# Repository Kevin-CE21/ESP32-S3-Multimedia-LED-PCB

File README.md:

# ESP32-S3 Multimedia & LED Control PCB (KiCad)

A 2-layer, heart-shaped carrier PCB that combines an ESP32-S3, 28 PWM-dimmed LEDs, a TFT display with microSD, and I2S audio on one USB-C-powered board. Designed from scratch in KiCad, from schematic through layout.

## PCB Layout

## Schematic

## 3D Model

## Board (Front)

## Board (Back)

## Overview

The board is a carrier for an ESP32-S3-DevKitC-1 module. It takes 5 V from a USB-C connector, drives 28 LEDs through two daisy-chained TLC5940 16-channel PWM drivers, shows graphics on an ILI9341 TFT, reads files from that display's microSD slot, and plays audio through a MAX98357A I2S class-D amplifier and speaker. Two pushbuttons provide user input.

## Hardware

| Ref | Part | Role |
| --- | --- | --- |
| U6 | ESP32-S3-DevKitC-1-N16R8V | Microcontroller, Wi-Fi, 3.3 V logic supply |
| U2, U4 | TLC5940NT | 16-channel, 12-bit PWM constant-current LED drivers (daisy-chained) |
| D1–D28 | LEDs | 28 PWM-controlled LEDs |
| U1 | ILI9341 TFT module with microSD | Display and file storage over SPI |
| U5 | MAX98357A (Adafruit 3006) | I2S class-D audio amplifier |
| J3 | USB-C receptacle (power only) | 5 V input |
| R1, R2 | 5.1 kΩ | USB-C CC pull-downs (power sink) |
| R3, R4 | 3.9 kΩ | TLC5940 IREF current-set resistors |
| C4, C5, C9, C10 | 100 nF | Local decoupling |
| C2 | 10 µF | Bulk capacitance |
| SW1, SW2 | Pushbuttons | User input |

## System Design

**Power**
- USB-C power-only receptacle with 5.1 kΩ pull-downs on CC1 and CC2, so any USB-C charger supplies 5 V.
- 5 V feeds the LED drivers, LEDs and audio amplifier; the DevKitC's onboard regulator supplies 3.3 V to logic.
- 100 nF decoupling at each IC plus 10 µF bulk capacitance.

**LED control**
- Two TLC5940s chained on one serial bus: the ESP32 shifts data into the first driver (SIN), and its SOUT feeds the second. Shared SCLK, XLAT, BLANK and GSCLK lines control both.
- 28 of the 32 available channels drive LEDs (all 16 on one driver, 12 on the other).
- Per-channel current is set by the IREF resistor: I = (1.24 V / 3.9 kΩ) × 31.5 ≈ 10 mA, about 280 mA with every LED fully on.

**Display and storage**
- The TFT and microSD share one SPI bus (SCK, MOSI, MISO) with separate chip selects (CS, SD_CS) plus D/C and RESET lines for the display.

**Audio**
- Dedicated I2S lines (BCLK, LRCLK, DIN) from the ESP32 to the MAX98357A, which drives the speaker directly.

## Design Considerations

- Trace widths sized to current: wider traces for 5 V power and LED loads, 0.5 mm traces for logic signals.
- Power and high-current paths kept short; decoupling placed next to each driver.
- ERC and DRC checks run before fabrication.

## Repository Contents

- `hardware/SosoGift.kicad_sch`: schematic
- `hardware/SosoGift.kicad_pro`: KiCad project file
- `images/`: layout, schematic and 3D renders

## Skills Demonstrated

- Schematic capture and PCB layout in KiCad
- Power input design (USB-C sink) and power distribution
- Constant-current LED driver design and current budgeting
- SPI and I2S peripheral integration
- Component selection and design rule verification

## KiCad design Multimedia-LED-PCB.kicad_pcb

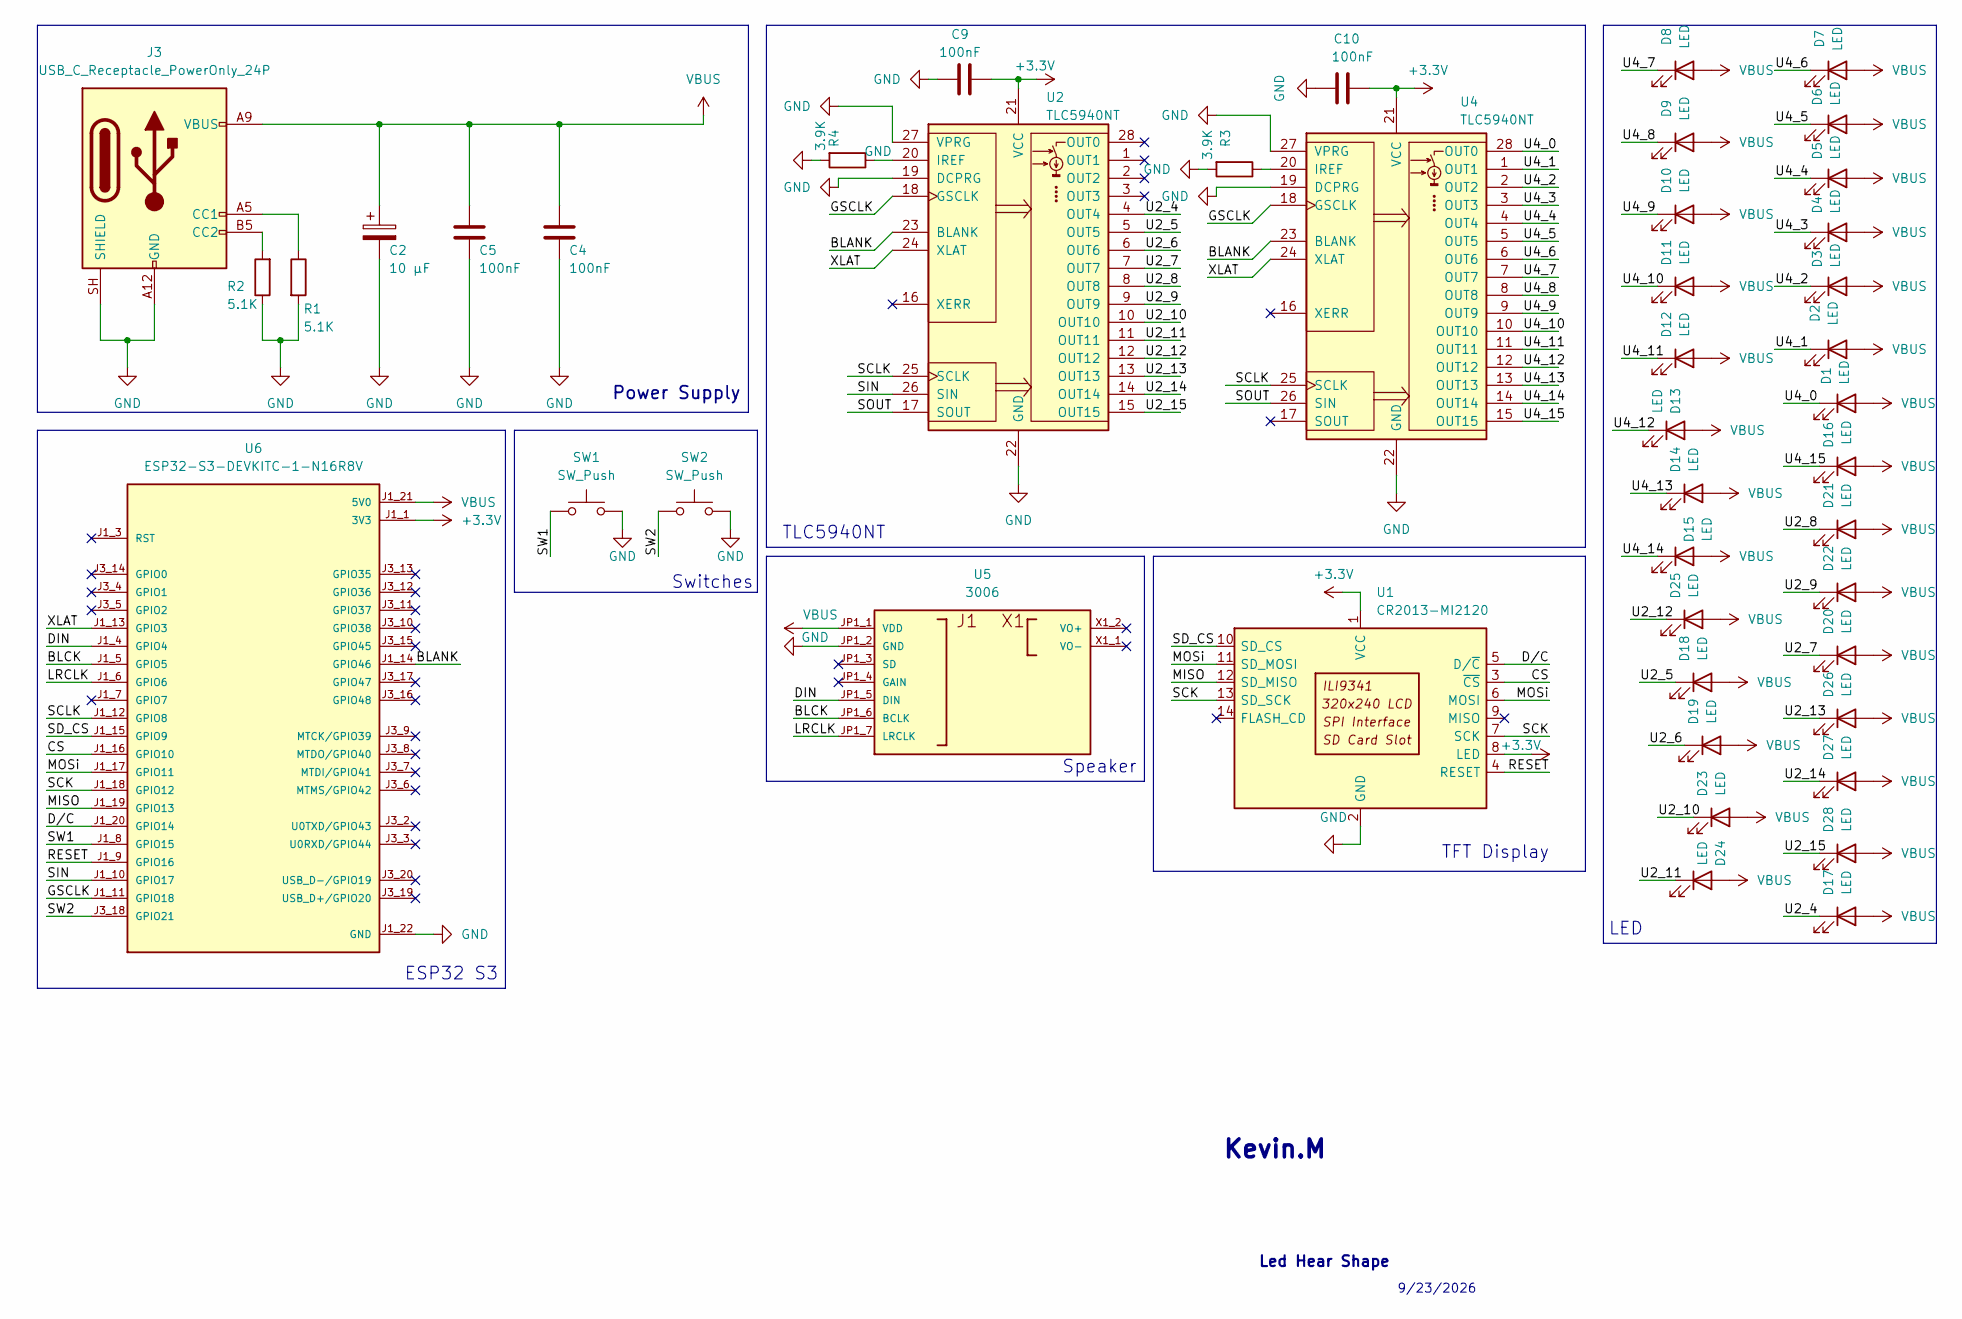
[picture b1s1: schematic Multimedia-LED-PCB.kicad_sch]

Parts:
C2: 10 µF; C_0805_2012Metric
C4, C5, C9, C10: 100nF; C_0603_1608Metric
D1, D2, D3, D4, D5, D6, D7, D8, D9, D10, D11, D12, D13, D14, D15, D16, D17, D18, D19, D20, D21, D22, D23, D24, D25, D26, D27, D28: LED; LED_D5.0mm
J3: USB_C_Receptacle_PowerOnly_24P; USB_C_Receptacle_GCT_USB4135-GF-A_6P_TopMnt_Horizontal; Part# C5438410
R1, R2: 5.1K; R_0603_1608Metric
R3, R4: 3.9K; R_0603_1608Metric
SW1, SW2: SW_Push; SW_PUSH-12mm
U1: CR2013-MI2120
U2, U4: TLC5940NT; DIP-28_W7.62mm
U5: 3006; MODULE_3006; PARTREV A
U6: ESP32-S3-DEVKITC-1-N16R8V; XCVR_ESP32-S3-DEVKITC-1-N16R8V; PARTREV 1.1

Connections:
+3.3V: C9.2, C10.2, U1.1 (VCC), U1.8 (LED), U2.21 (VCC), U4.21 (VCC), U6.J1_1 (3V3), U6.J1_2 (3V3)
/BLANK: U2.23 (BLANK), U4.23 (BLANK), U6.J1_14 (GPIO46)
/BLCK: U5.JP1_6 (BCLK), U6.J1_5 (GPIO5)
/CS: U1.3 (~CS), U6.J1_16 (GPIO10)
/DIN: U5.JP1_5 (DIN), U6.J1_4 (GPIO4)
/D/C: U1.5 (D/~C), U6.J1_20 (GPIO14)
/GSCLK: U2.18 (GSCLK), U4.18 (GSCLK), U6.J1_11 (GPIO18)
/LRCLK: U5.JP1_7 (LRCLK), U6.J1_6 (GPIO6)
/MISO: U1.12 (SD_MISO), U6.J1_19 (GPIO13)
/MOSi: U1.6 (MOSI), U1.11 (SD_MOSI), U6.J1_17 (GPIO11)
/RESET: U1.4 (RESET), U6.J1_9 (GPIO16)
/SCK: U1.7 (SCK), U1.13 (SD_SCK), U6.J1_18 (GPIO12)
/SCLK: U2.25 (SCLK), U4.25 (SCLK), U6.J1_12 (GPIO8)
/SD_CS: U1.10 (SD_CS), U6.J1_15 (GPIO9)
/SIN: U2.26 (SIN), U6.J1_10 (GPIO17)
/SOUT: U2.17 (SOUT), U4.26 (SIN)
/SW1: SW1.1, U6.J1_8 (GPIO15)
/SW2: SW2.1, U6.J3_18 (GPIO21)
/U2_4: D17.1 (K), U2.4 (OUT4)
/U2_5: D18.1 (K), U2.5 (OUT5)
/U2_6: D19.1 (K), U2.6 (OUT6)
/U2_7: D20.1 (K), U2.7 (OUT7)
/U2_8: D21.1 (K), U2.8 (OUT8)
/U2_9: D22.1 (K), U2.9 (OUT9)
/U2_10: D23.1 (K), U2.10 (OUT10)
/U2_11: D24.1 (K), U2.11 (OUT11)
/U2_12: D25.1 (K), U2.12 (OUT12)
/U2_13: D26.1 (K), U2.13 (OUT13)
/U2_14: D27.1 (K), U2.14 (OUT14)
/U2_15: D28.1 (K), U2.15 (OUT15)
/U4_0: D1.1 (K), U4.28 (OUT0)
/U4_1: D2.1 (K), U4.1 (OUT1)
/U4_2: D3.1 (K), U4.2 (OUT2)
/U4_3: D4.1 (K), U4.3 (OUT3)
/U4_4: D5.1 (K), U4.4 (OUT4)
/U4_5: D6.1 (K), U4.5 (OUT5)
/U4_6: D7.1 (K), U4.6 (OUT6)
/U4_7: D8.1 (K), U4.7 (OUT7)
/U4_8: D9.1 (K), U4.8 (OUT8)
/U4_9: D10.1 (K), U4.9 (OUT9)
/U4_10: D11.1 (K), U4.10 (OUT10)
/U4_11: D12.1 (K), U4.11 (OUT11)
/U4_12: D13.1 (K), U4.12 (OUT12)
/U4_13: D14.1 (K), U4.13 (OUT13)
/U4_14: D15.1 (K), U4.14 (OUT14)
/U4_15: D16.1 (K), U4.15 (OUT15)
/XLAT: U2.24 (XLAT), U4.24 (XLAT), U6.J1_13 (GPIO3)
GND: C2.2, C4.2, C5.2, C9.1, C10.1, J3.A1 (GND), J3.A12 (GND), J3.B1 (GND), J3.B12 (GND), J3.SH (SHIELD), R1.2, R2.1, R3.2, R4.2, SW1.2, SW2.2, U1.2 (GND), U2.19 (DCPRG), U2.22 (GND), U2.27 (VPRG), U4.19 (DCPRG), U4.22 (GND), U4.27 (VPRG), U5.JP1_2 (GND), U6.J1_22 (GND), U6.J3_1 (GND), U6.J3_21 (GND), U6.J3_22 (GND)
unnamed: J3.A5 (CC1), R1.1
unnamed: J3.B5 (CC2), R2.2
unnamed: R4.1, U2.20 (IREF)
unnamed: R3.1, U4.20 (IREF)
VBUS: C2.1, C4.1, C5.1, D1.2 (A), D2.2 (A), D3.2 (A), D4.2 (A), D5.2 (A), D6.2 (A), D7.2 (A), D8.2 (A), D9.2 (A), D10.2 (A), D11.2 (A), D12.2 (A), D13.2 (A), D14.2 (A), D15.2 (A), D16.2 (A), D17.2 (A), D18.2 (A), D19.2 (A), D20.2 (A), D21.2 (A), D22.2 (A), D23.2 (A), D24.2 (A), D25.2 (A), D26.2 (A), D27.2 (A), D28.2 (A), J3.A4 (VBUS), J3.A9 (VBUS), J3.B4 (VBUS), J3.B9 (VBUS), U5.JP1_1 (VDD), U6.J1_21 (5V0)

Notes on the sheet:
Led Hear Shape
LED
TLC5940NT
Kevin.M
9/23/2026
TFT Display
Speaker
Power Supply
Switches
ESP32 S3

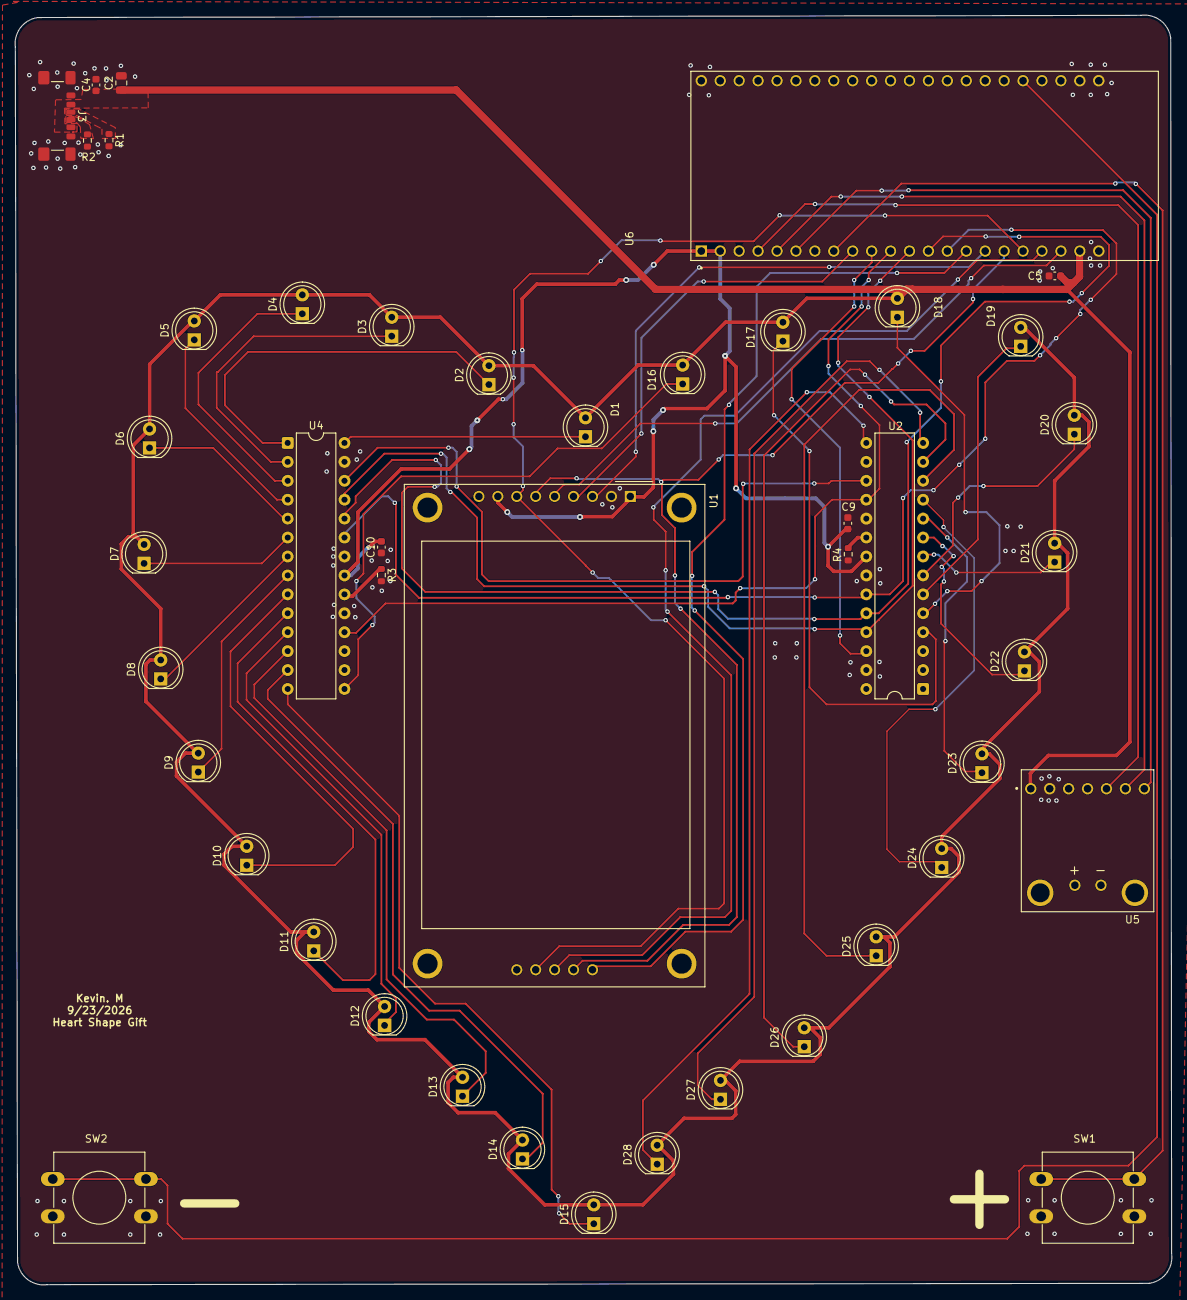
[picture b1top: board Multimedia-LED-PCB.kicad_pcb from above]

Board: 2 copper layers, 155.2 x 170.4 mm, 45 parts (0 on the bottom side), 53 nets.
